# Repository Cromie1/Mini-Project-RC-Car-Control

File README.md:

# Mini-Project-RC-Car-Control
Names: 
Alex Cromar,
Kyla Kunz,
Mike Mercer

# E-Maxx Mirage
The motivation for this project stems from our senior project, E-Maxx Mirage, which involves mounting a camera onto the RC car and linking it to a VR headset. In the final version of the senior project, we will be using Xbox wheels and pedals to enhance the driving experience. However, for the sake of simplicity and proof of concept, the initial focus is on implementing a Wii nunchuck to control the car.

# Purpose and Functionality
This project revolves around utilizing a Wii nunchuck to control an RC car. The communication between the Wii nunchuck and the STM microcontroller is through I2C protocol. Interrupts are also be used to enhance the efficiency of the I2C communication process. The input from the Nunchuck is used to change values on the digital potentiometers, which then communicates with the orginal transmitter for the car. Two PCB boards were also created to replace the breadboard, but the boards did not work as expected. The car moves forward by pressing "C", backwards by pressing "Z" and turns left and right based off of the joystick input.

# Instructions
To begin use with the breadboard design the user must connect the stm microcontroller to the following pins. Red 5v to the 5v pin. Black gnd to the gnd pin. Yellow first yellow wire to the SCL pin. Orange wire to SDA pin. Second yellow wire to the 3v pin. 

After connecting all the necessary wires the user must then plug in the transmitter to power and turn on the transmitter. At this point, the LEDs on the breakout boards should be on and the transmitter LED should be on. The user can then turn on the RC car and adjust the trim potentiometers on the transmitter to ensure alignment is correct. After this, the care should be fully functional. The user must make sure that the antenna is not fully extended otherwise radio interference will cause the I2C  Singals to not work properly.
# Wiring Diagram
The wiring diagram for the shematic 

# Schematics
Two schematics were created for this project unfortunately neither design worked and would require a redesign.

This is the schematic for the basic implementation. There is not change being done to the input voltage for the digital potentiometer.

This is the finished version of the first design.

This design utilizes zener diodes to drop the input voltages into the digital potentiometers. 
This was done to decrease the range so that we could input finer granularity into the control of the car.

This is the completed board for the second design.
# Flowcharts
Here is the flow of data over the I2C line.

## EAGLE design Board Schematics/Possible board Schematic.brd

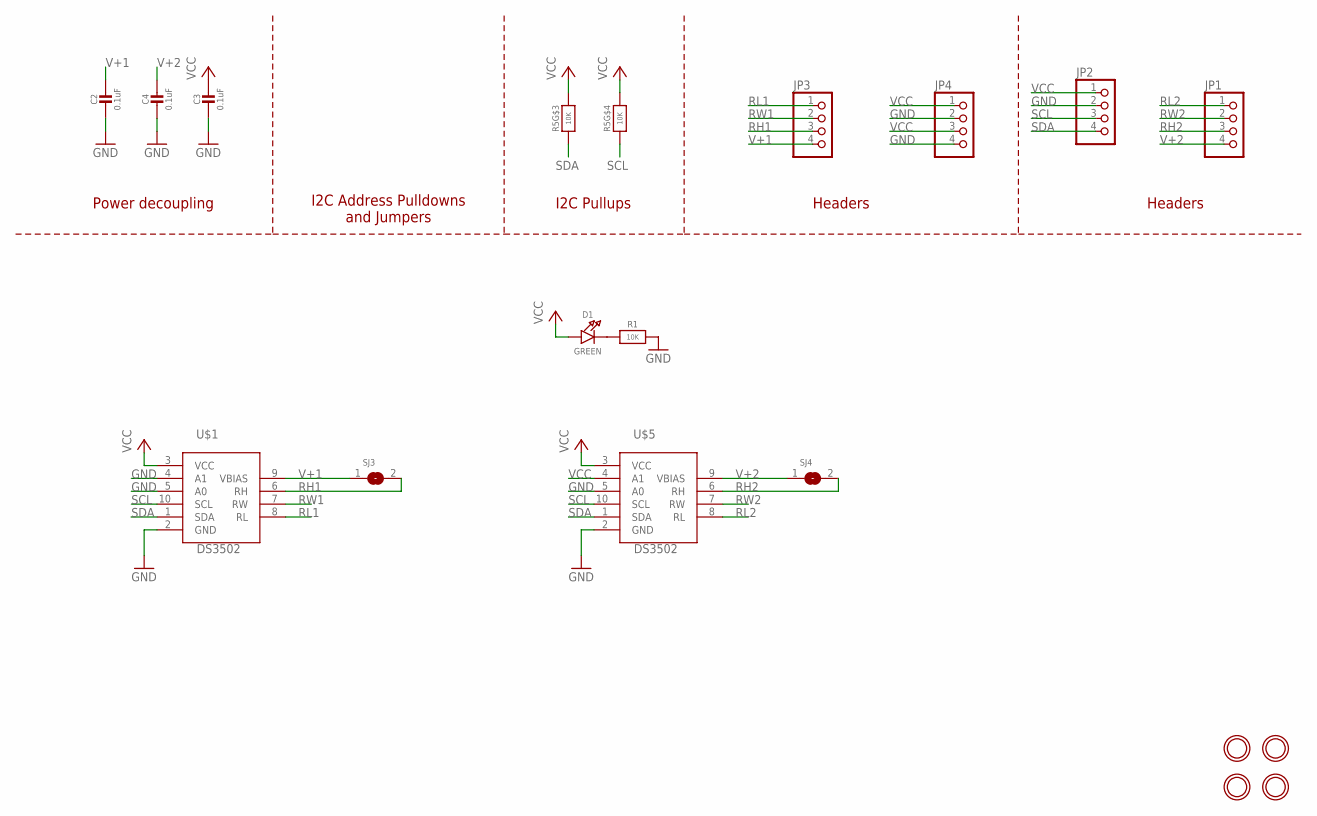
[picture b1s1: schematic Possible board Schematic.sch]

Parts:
C2, C3, C4: 0.1uF; 0603-NO
D1: GREEN; CHIPLED_0603_NOOUTLINE
JP1, JP2, JP3, JP4: HEADER-1X4ROUND; 1X04_ROUND
R1: 10K; 0603-NO
R5: 10K; RESPACK_4X0603
SJ3, SJ4: SOLDERJUMPERCLOSED; SOLDERJUMPER_CLOSEDWIRE
U$1, U$5: DS3502; MSOP10
U$2, U$3, U$6, U$7: MOUNTINGHOLE2.5; MOUNTINGHOLE_2.5_PLATED

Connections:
GND: C2.2, C3.2, C4.2, JP2.2, JP4.2, JP4.4, R1.2, U$1.2 (GND), U$1.4 (A1), U$1.5 (A0), U$5.2 (GND), U$5.5 (A0)
unnamed: D1.C, R1.1
RH1: JP3.3, SJ3.2, U$1.6 (RH)
RH2: JP1.3, SJ4.2, U$5.6 (RH)
RL1: JP3.1, U$1.8 (RL)
RL2: JP1.1, U$5.8 (RL)
RW1: JP3.2, U$1.7 (RW)
RW2: JP1.2, U$5.7 (RW)
SCL: JP2.3, R5.4 (1), U$1.10 (SCL), U$5.10 (SCL)
SDA: JP2.4, R5.3 (1), U$1.1 (SDA), U$5.1 (SDA)
V+1: C2.1, JP3.4, SJ3.1, U$1.9 (VBIAS)
V+2: C4.1, JP1.4, SJ4.1, U$5.9 (VBIAS)
VCC: C3.1, D1.A, JP2.1, JP4.1, JP4.3, R5.5 (2), R5.6 (2), U$1.3 (VCC), U$5.3 (VCC), U$5.4 (A1)

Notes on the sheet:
I2C Address Pulldowns and Jumpers
Power decoupling
I2C Pullups
Headers

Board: 2 copper layers, 18 parts (0 on the bottom side), 13 nets, no tracks yet.

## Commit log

2024-03-21 Started Project
    Started Project, this has the car control c code that has been written so far. The code so far is untested but should be able to initialize the Wii Nunchuck.
2024-03-21 Added my name to the README
2024-03-21 Added Helpful Documentation
2024-03-21 Writing to Nunchuck
    Tested writing to nunchuck. May need to fix interrupts.
2024-03-21 Working Nunchuck Reading!
2024-03-21 Nunchuck LED's
    Nunchuck controls now control LED's on the board.
2024-03-21 Can now control steering pot with nunchuck
2024-03-21 added Kyla to README
2024-03-23 Update README.md
    Mike's commit
2024-03-26 Added Schematic files
    Need to start constructing board.
2024-03-26 Started a board schematic
2024-03-26 Able to drive car with limited functionality.
2024-03-26 Started Board Schemate
2024-03-27 Wired together possible board schematic #1
2024-03-28 Finished schematic with zener diodes
2024-03-28 Made small changes to clean code.
2024-03-28 Added Granularity to Steering control.
2024-04-18 Code cleanup
    Cleaned comments and redundant code. Full functionality should work. With nunchuck.
2024-04-25 Added photos folder
2024-04-25 Added images for PCB Designs and soldered PCBs
2024-04-25 Added to readme
2024-04-25 Added more photos
2024-04-25 Added text to the schematics section of the README.md
2024-04-26 Introduction and puspose on readme
2024-04-26 Added the wiring diagram
2024-04-26 Rename Wiring Diagram.png to Wiring_Diagram.png
2024-04-26 added a flow

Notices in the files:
parts and their libraries:
microbuilder: This work is placed in the public domain, and may be freely used for commercial and non-commercial work with the following conditions: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
